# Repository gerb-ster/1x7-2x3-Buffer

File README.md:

# 2×3 – 1×7 Buffer

A simple but effective little module. An active buffer build around the TL074 & TL072 IC’s. The output of the last output of the first block is linked to the input of the second block. So when there is nothing connected to the second input you have a 1×7 buffer.

Ps. On the silkscreen is a small typo; it should note “2×3 / 1×7” instead of “2×3 / 1×6”, this is fixed in the schematics & PCB design.

## Status: Finished

- done: first schematic & board design
- done: breadboard and test
- done: design frontpanel
- done: order PCB and build prototype

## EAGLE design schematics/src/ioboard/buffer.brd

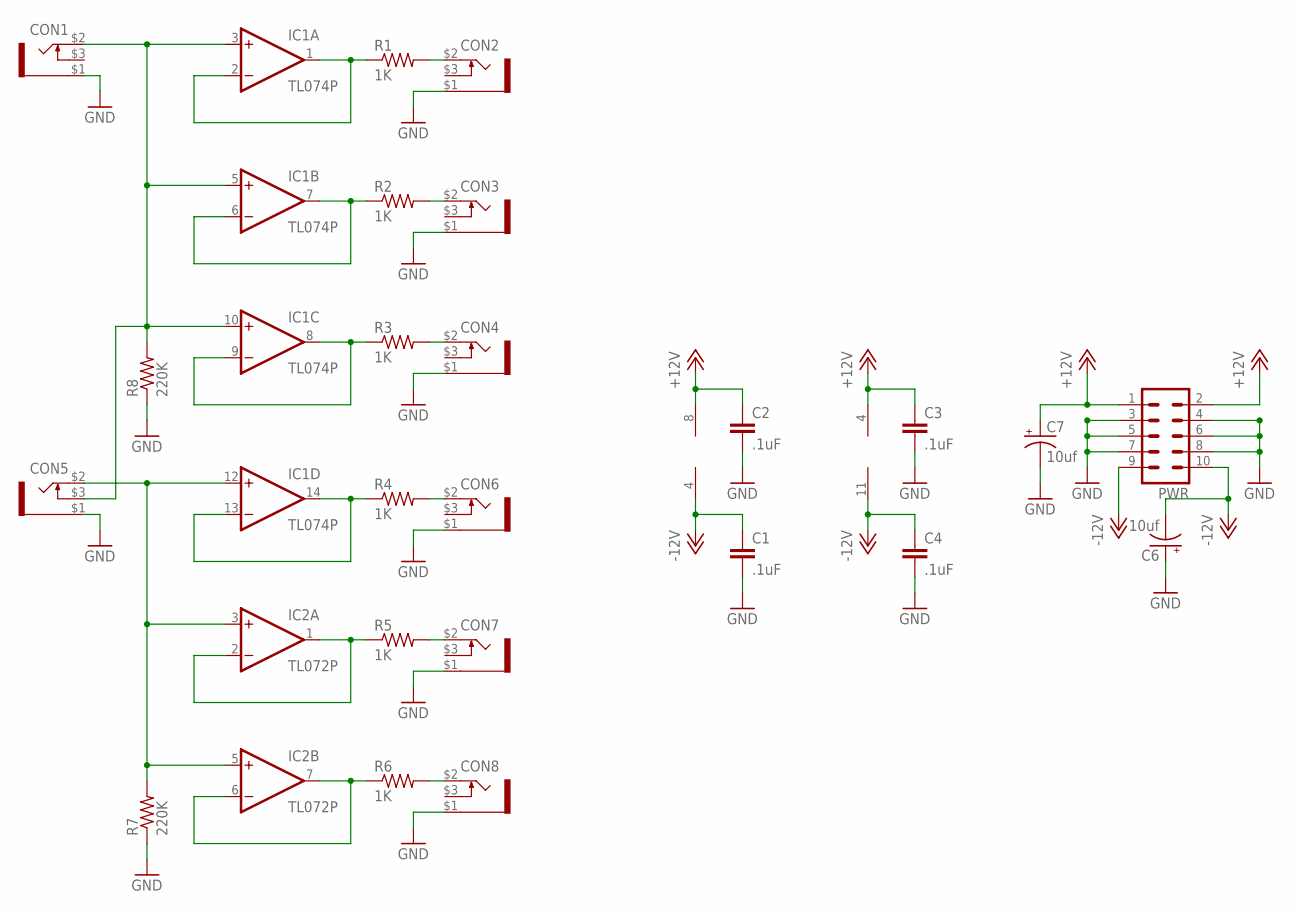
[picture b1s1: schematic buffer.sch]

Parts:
C1, C2, C3, C4: .1uF; C050-024X044
C6, C7: 10uf; E2,5-5
CON1, CON2, CON3, CON4, CON5, CON6, CON7, CON8: PJ-323PJ-323; PJ-323
IC1: TL074P; DIL14
IC2: TL072P; DIL08
PWR: ML10
R1, R2, R3, R4, R5, R6: 1K; 0207/2V
R7, R8: 220K; 0207/2V

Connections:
+12V: C2.1, C3.1, C7.+, IC1.4 (V+), IC2.8 (V+), PWR.1, PWR.2
-12V: C1.1, C4.1, C6.-, IC1.11 (V-), IC2.4 (V-), PWR.9, PWR.10
GND: C1.2, C2.2, C3.2, C4.2, C6.+, C7.-, CON1.$1 (3), CON2.$1 (3), CON3.$1 (3), CON4.$1 (3), CON5.$1 (3), CON6.$1 (3), CON7.$1 (3), CON8.$1 (3), PWR.3, PWR.4, PWR.5, PWR.6, PWR.7, PWR.8, R7.1, R8.1
unnamed: CON1.$2 (1), CON5.$3 (2), IC1.3 (+IN), IC1.5 (+IN), IC1.10 (+IN), R8.2
unnamed: IC1.8 (OUT), IC1.9 (-IN), R3.1
unnamed: IC1.6 (-IN), IC1.7 (OUT), R2.1
unnamed: IC1.1 (OUT), IC1.2 (-IN), R1.1
unnamed: CON5.$2 (1), IC1.12 (+IN), IC2.3 (+IN), IC2.5 (+IN), R7.2
unnamed: CON4.$2 (1), R3.2
unnamed: CON6.$2 (1), R4.2
unnamed: IC1.13 (-IN), IC1.14 (OUT), R4.1
unnamed: IC2.1 (OUT), IC2.2 (-IN), R5.1
unnamed: IC2.6 (-IN), IC2.7 (OUT), R6.1
unnamed: CON7.$2 (1), R5.2
unnamed: CON3.$2 (1), R2.2
unnamed: CON2.$2 (1), R1.2
unnamed: CON8.$2 (1), R6.2

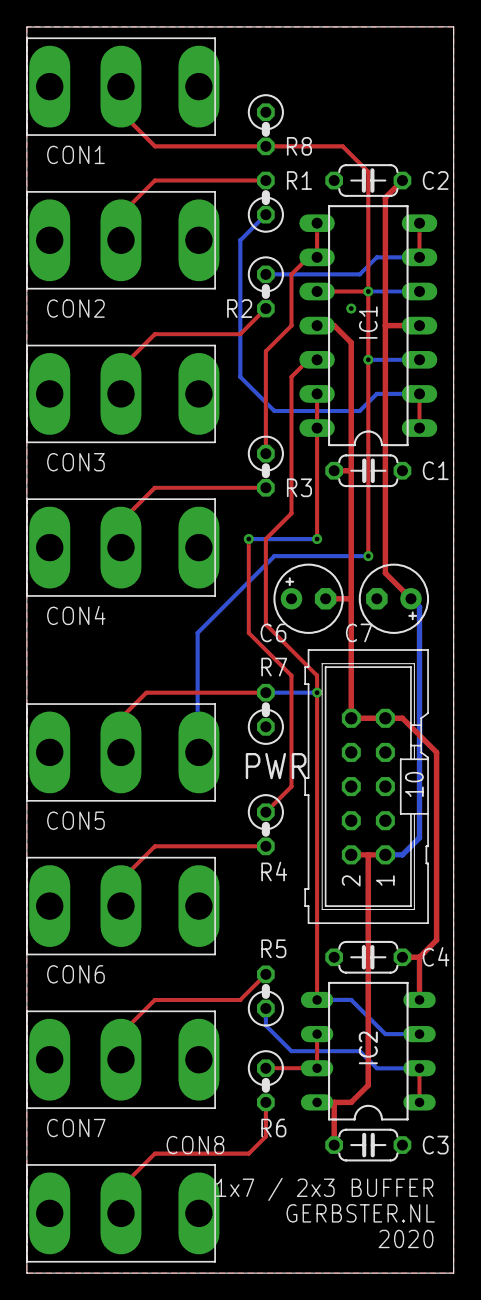
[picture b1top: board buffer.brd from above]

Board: 2 copper layers, 31.8 x 92.7 mm, 25 parts (0 on the bottom side), 17 nets.

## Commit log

2021-05-06 some files
2021-05-07 Added files & structure
2021-05-10 Added Status
2021-05-11 Added Status & Images
2021-08-06 Updated some schematics and docs
2021-08-10 Fixed some bugs and updated documentation
2022-04-20 Some updates & bugfixes
2022-04-22 Fixed schematics & descriptions
2022-05-17 Updated Firmware
2022-05-18 Updated Faceplates
2022-05-18 Fixed issues
2022-05-21 Fixed schematics
2022-05-28 General updates
